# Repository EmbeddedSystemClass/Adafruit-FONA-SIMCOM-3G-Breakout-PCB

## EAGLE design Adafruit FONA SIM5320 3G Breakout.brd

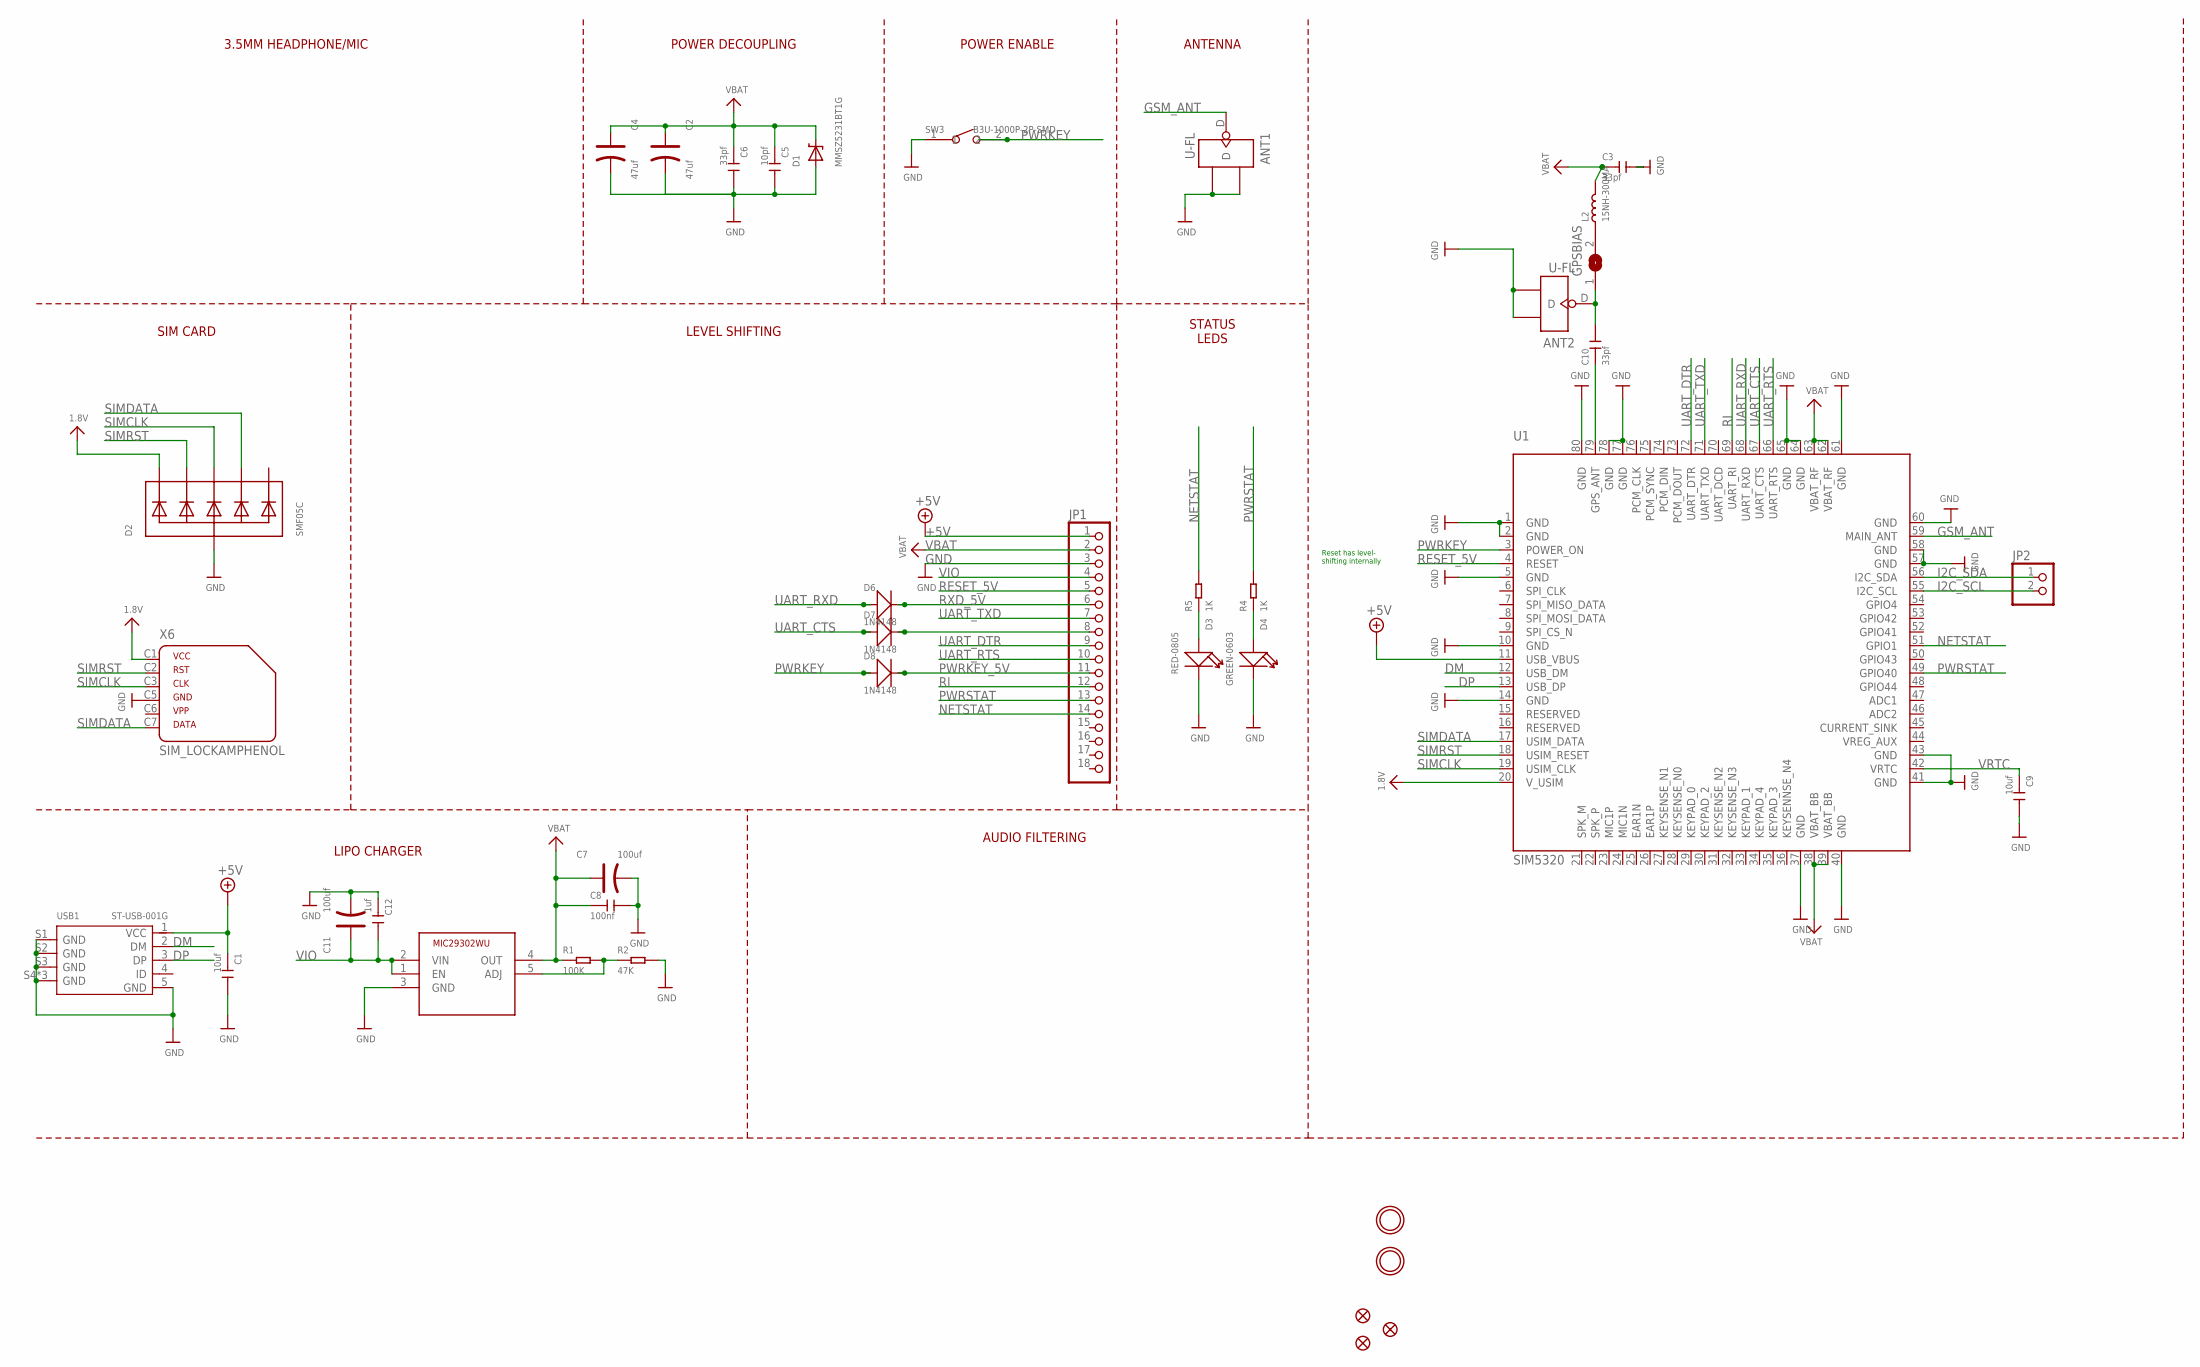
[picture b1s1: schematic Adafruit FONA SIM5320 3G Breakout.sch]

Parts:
ANT1, ANT2: U-FL; U-FL3P-SMD-2.6X2.6X1.0MM
C1: 10uf; C0603
C2, C4: 47uf; AVX-B
C3, C6, C10: 33pf; C0402
C5: 10pf; C0402
C7, C11: 100uf; AVX-B
C8: 100nf; C0402
C9: 10uf; C0805
C12: 1uf; C0603
D1: MMSZ5231BT1G; SOD-123
D2: SMF05C; SOT363
D3: RED-0805; LED-0805
D4: GREEN-0603; LED-0603
D6, D7, D8: 1N4148; LL-34
FID1, FID4, FID5: FIDUCIAL""; FIDUCIAL_1MM
GPSBIAS: SOLDERJUMPER; SOLDERJUMPER_ARROW_NOPASTE
IC1: MIC29302WU; TO263-5
JP1: HEADER-1X18; 1X18_ROUND70
JP2: HEADER-1X2ROUND; 1X02_ROUND
L2: 15NH-300MA; L0402
R1: 100K; R0603
R2: 47K; R0603
R4, R5: 1K; R0603
SW3: B3U-1000P-2P-SMD; SW2-2.6-3.0X2.5X1.2+0.4MM
U1: SIM5320
U$33, U$34: MOUNTINGHOLE2.5; MOUNTINGHOLE_2.5_PLATED
USB1: ST-USB-001G; MICRO-USB5+4P-SMD-0.65-B
X6: SIM_LOCKAMPHENOL; C707_10M006_512_2

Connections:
1.8V: D2.1 (C1), U1.20 (V_USIM), X6.C1 (1)
+5V: C1.1, JP1.1, U1.11 (USB_VBUS), USB1.1 (VCC)
CTS_5V: D7.C (-), JP1.8
DM: U1.12 (USB_DM), USB1.2 (DM)
DP: U1.13 (USB_DP), USB1.3 (DP)
GND: ANT1.GND1, ANT1.GND2, ANT2.GND1, ANT2.GND2, C1.2, C2.-, C3.2, C4.-, C5.2, C6.2, C7.-, C8.2, C9.2, C11.-, C12.1, D1.A, D2.2 (A), D3.-, D4.-, IC1.3 (GND), JP1.3, R2.2, SW3.1, U1.1 (GND), U1.2 (GND), U1.5 (GND), U1.10 (GND), U1.14 (GND), U1.37 (GND), U1.40 (GND), U1.41 (GND), U1.43 (GND), U1.57 (GND), U1.58 (GND), U1.60 (GND), U1.61 (GND), U1.64 (GND), U1.65 (GND), U1.77 (GND), U1.78 (GND), U1.80 (GND), USB1.5 (GND), USB1.S1 (GND), USB1.S2 (GND), USB1.S3 (GND), USB1.S4 (GND), USB1.S5 (GND), USB1.S6 (GND), X6.C5 (4)
GSM_ANT: ANT1.D, U1.59 (MAIN_ANT)
I2C_SCL: JP2.2, U1.55 (I2C_SCL)
I2C_SDA: JP2.1, U1.56 (I2C_SDA)
unnamed: IC1.5 (ADJ), R1.2, R2.1
unnamed: ANT2.D, C10.2, GPSBIAS.1
unnamed: D4.+, R4.1
unnamed: C10.1, U1.79 (GPS_ANT)
unnamed: D3.+, R5.1
unnamed: GPSBIAS.2, L2.1
NETSTAT: JP1.14, R5.2, U1.51 (GPIO1)
PWRKEY: D8.A (+), SW3.2, U1.3 (POWER_ON)
PWRKEY_5V: D8.C (-), JP1.11
PWRSTAT: JP1.13, R4.2, U1.49 (GPIO40)
RESET_5V: JP1.5, U1.4 (RESET)
RI: JP1.12, U1.69 (UART_RI)
RXD_5V: D6.C (-), JP1.6
SIMCLK: D2.4 (C3), U1.19 (USIM_CLK), X6.C3 (3)
SIMDATA: D2.5 (C4), U1.17 (USIM_DATA), X6.C7 (6)
SIMRST: D2.3 (C2), U1.18 (USIM_RESET), X6.C2 (2)
UART_CTS: D7.A (+), U1.67 (UART_CTS)
UART_DTR: JP1.9, U1.72 (UART_DTR)
UART_RTS: JP1.10, U1.66 (UART_RTS)
UART_RXD: D6.A (+), U1.68 (UART_RXD)
UART_TXD: JP1.7, U1.71 (UART_TXD)
VBAT: C2.+, C3.1, C4.+, C5.1, C6.1, C7.+, C8.1, D1.C, IC1.4 (OUT), JP1.2, L2.2, R1.1, U1.38 (VBAT_BB), U1.39 (VBAT_BB), U1.62 (VBAT_RF), U1.63 (VBAT_RF)
VIO: C11.+, C12.2, IC1.1 (EN), IC1.2 (VIN), JP1.4
VRTC: C9.1, U1.42 (VRTC)

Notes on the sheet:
ANTENNA
POWER DECOUPLING
3.5MM HEADPHONE/MIC
SIM CARD
LEVEL SHIFTING
LIPO CHARGER
AUDIO FILTERING
STATUS LEDS
POWER ENABLE
Reset has level- shifting internally

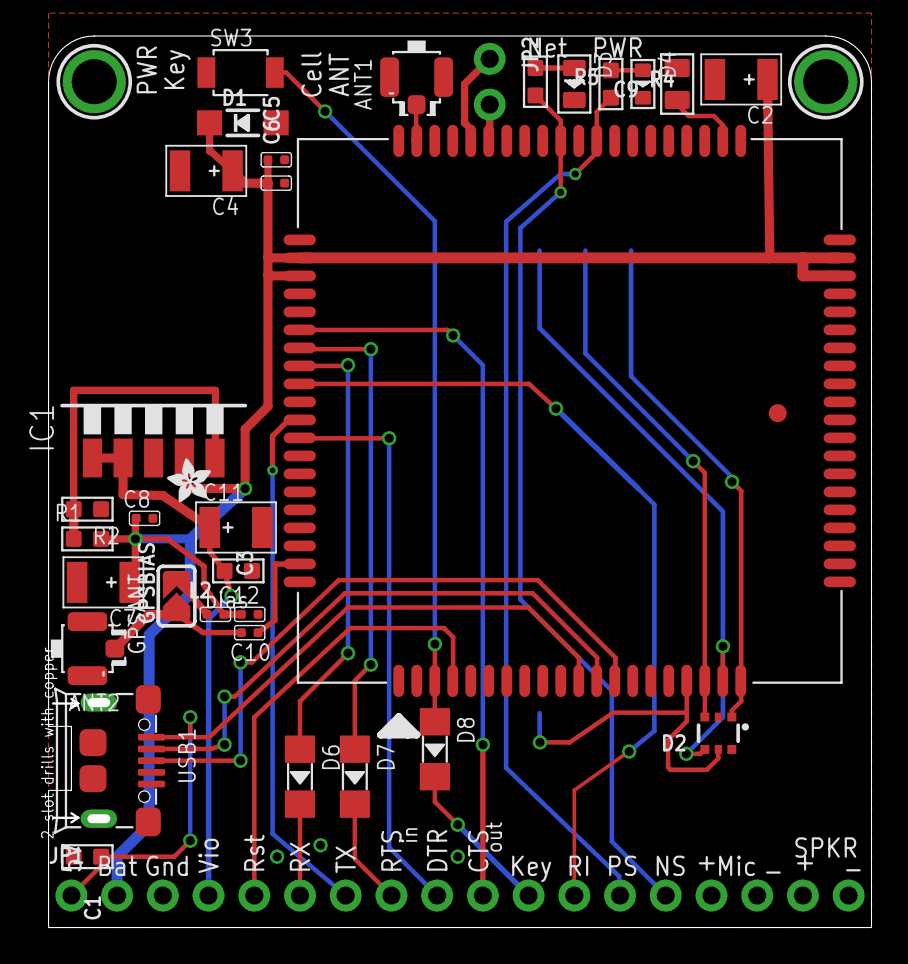
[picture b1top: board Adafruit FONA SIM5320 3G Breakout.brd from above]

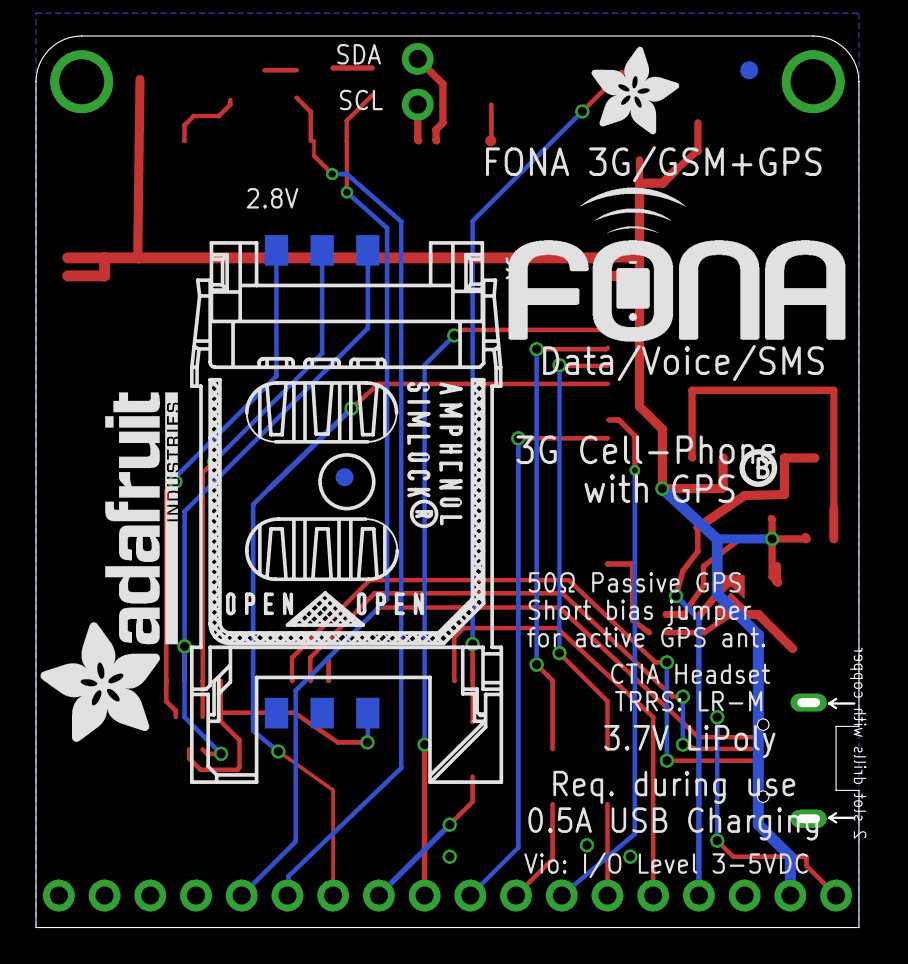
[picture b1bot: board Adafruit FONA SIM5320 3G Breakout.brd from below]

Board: 2 copper layers, 45.9 x 49.0 mm, 44 parts (7 on the bottom side), 33 nets.

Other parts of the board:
U$21: ADAFRUIT_2.5MM
U$25: PCBFEAT-REV-040
U$26: FONA_LOGO
U$36: ADAFRUIT_5MM
U$42: ADAFRUIT_TEXT_20MM

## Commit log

2017-08-06 最小構成
2017-08-07 部品をPCB Fusion化
2017-08-07 USBをPCBのパーツ化
2017-08-11 最小構成ver1.1.0
2017-08-11 最小構成ver1.1.1
2017-08-11 最小構成ver1.1.2
2017-08-11 最小構成ver1.1.3
2017-08-11 最小構成ver1.1.5

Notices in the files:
parts and their libraries:
microbuilder: This work is placed in the public domain, and may be freely used for commercial and non-commercial work with the following conditions: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
